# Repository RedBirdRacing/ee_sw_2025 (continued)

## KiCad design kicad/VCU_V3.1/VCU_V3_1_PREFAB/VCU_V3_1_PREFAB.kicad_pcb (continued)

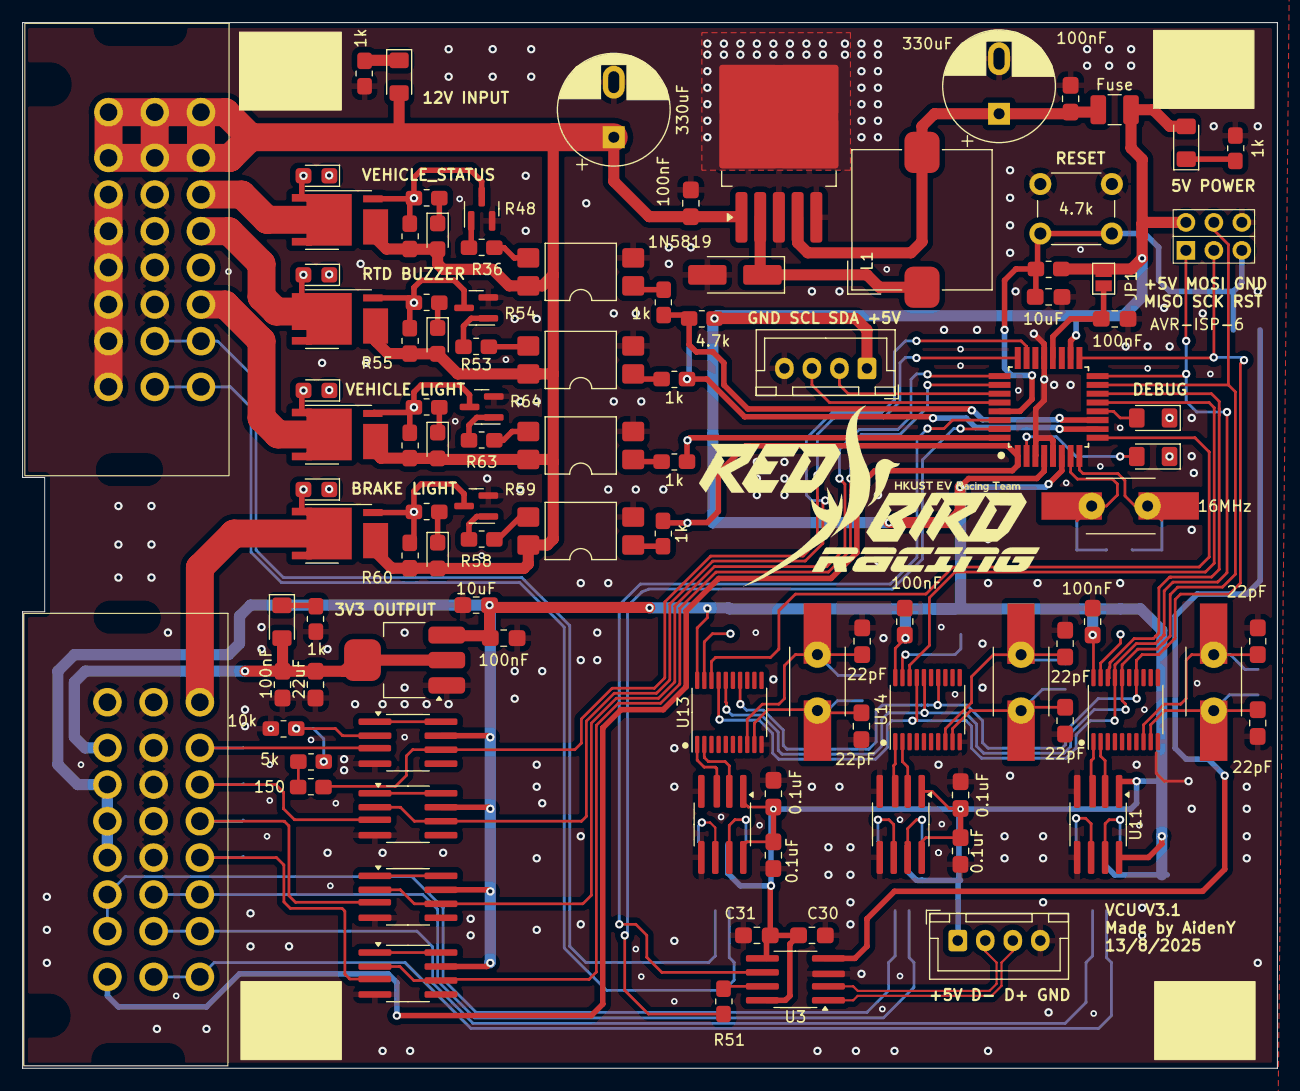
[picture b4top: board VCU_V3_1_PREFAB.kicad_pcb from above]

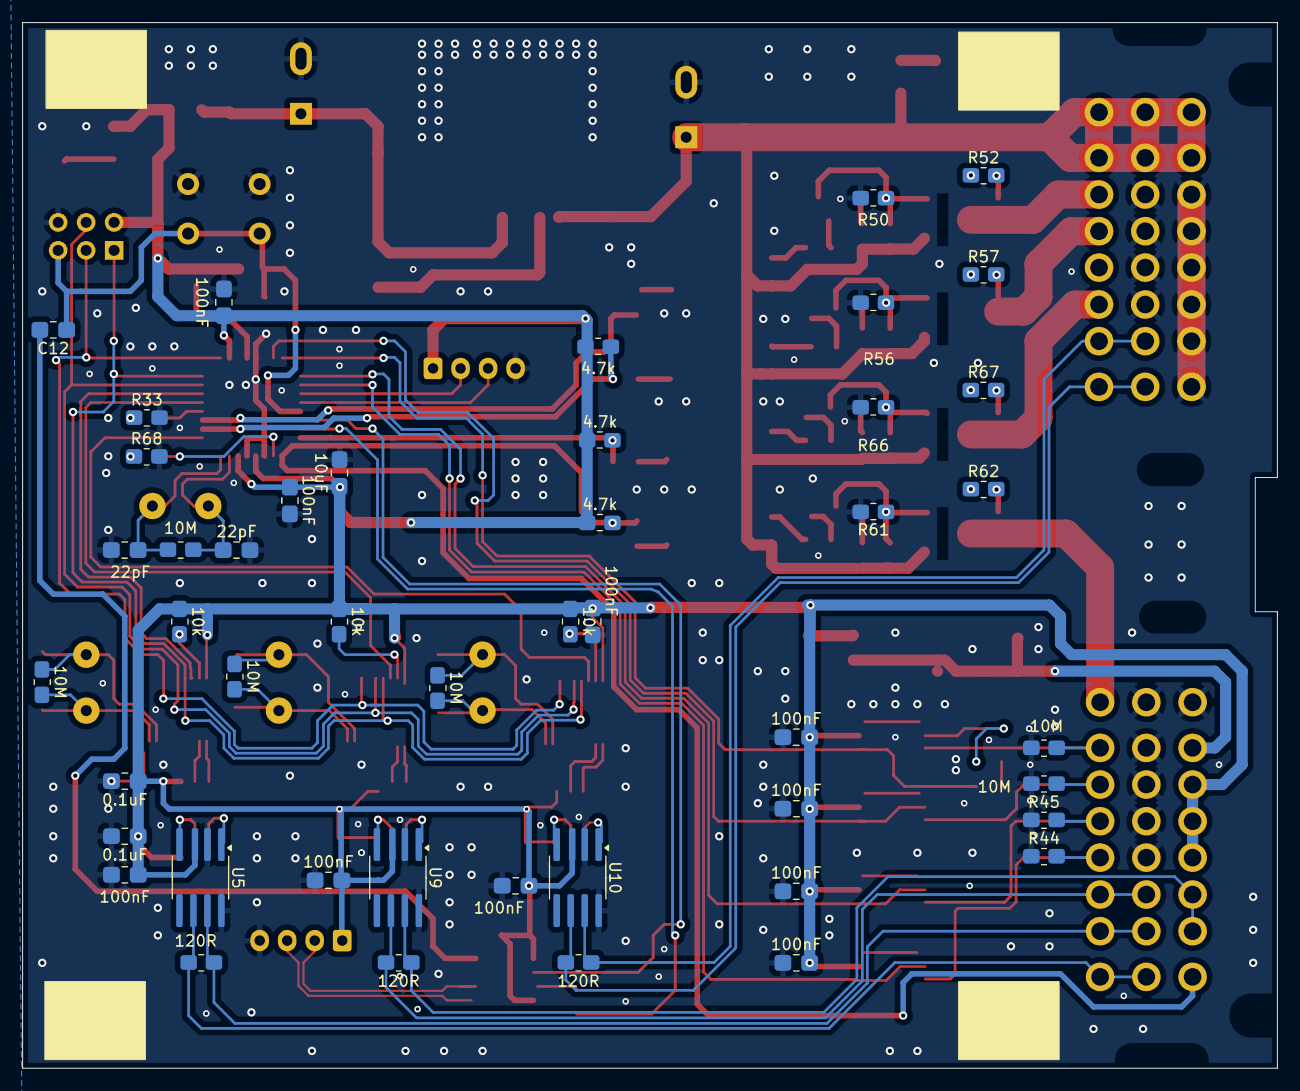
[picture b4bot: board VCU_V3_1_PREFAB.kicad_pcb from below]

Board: 2 copper layers, 114.0 x 95.0 mm, 152 parts (46 on the bottom side), 104 nets.

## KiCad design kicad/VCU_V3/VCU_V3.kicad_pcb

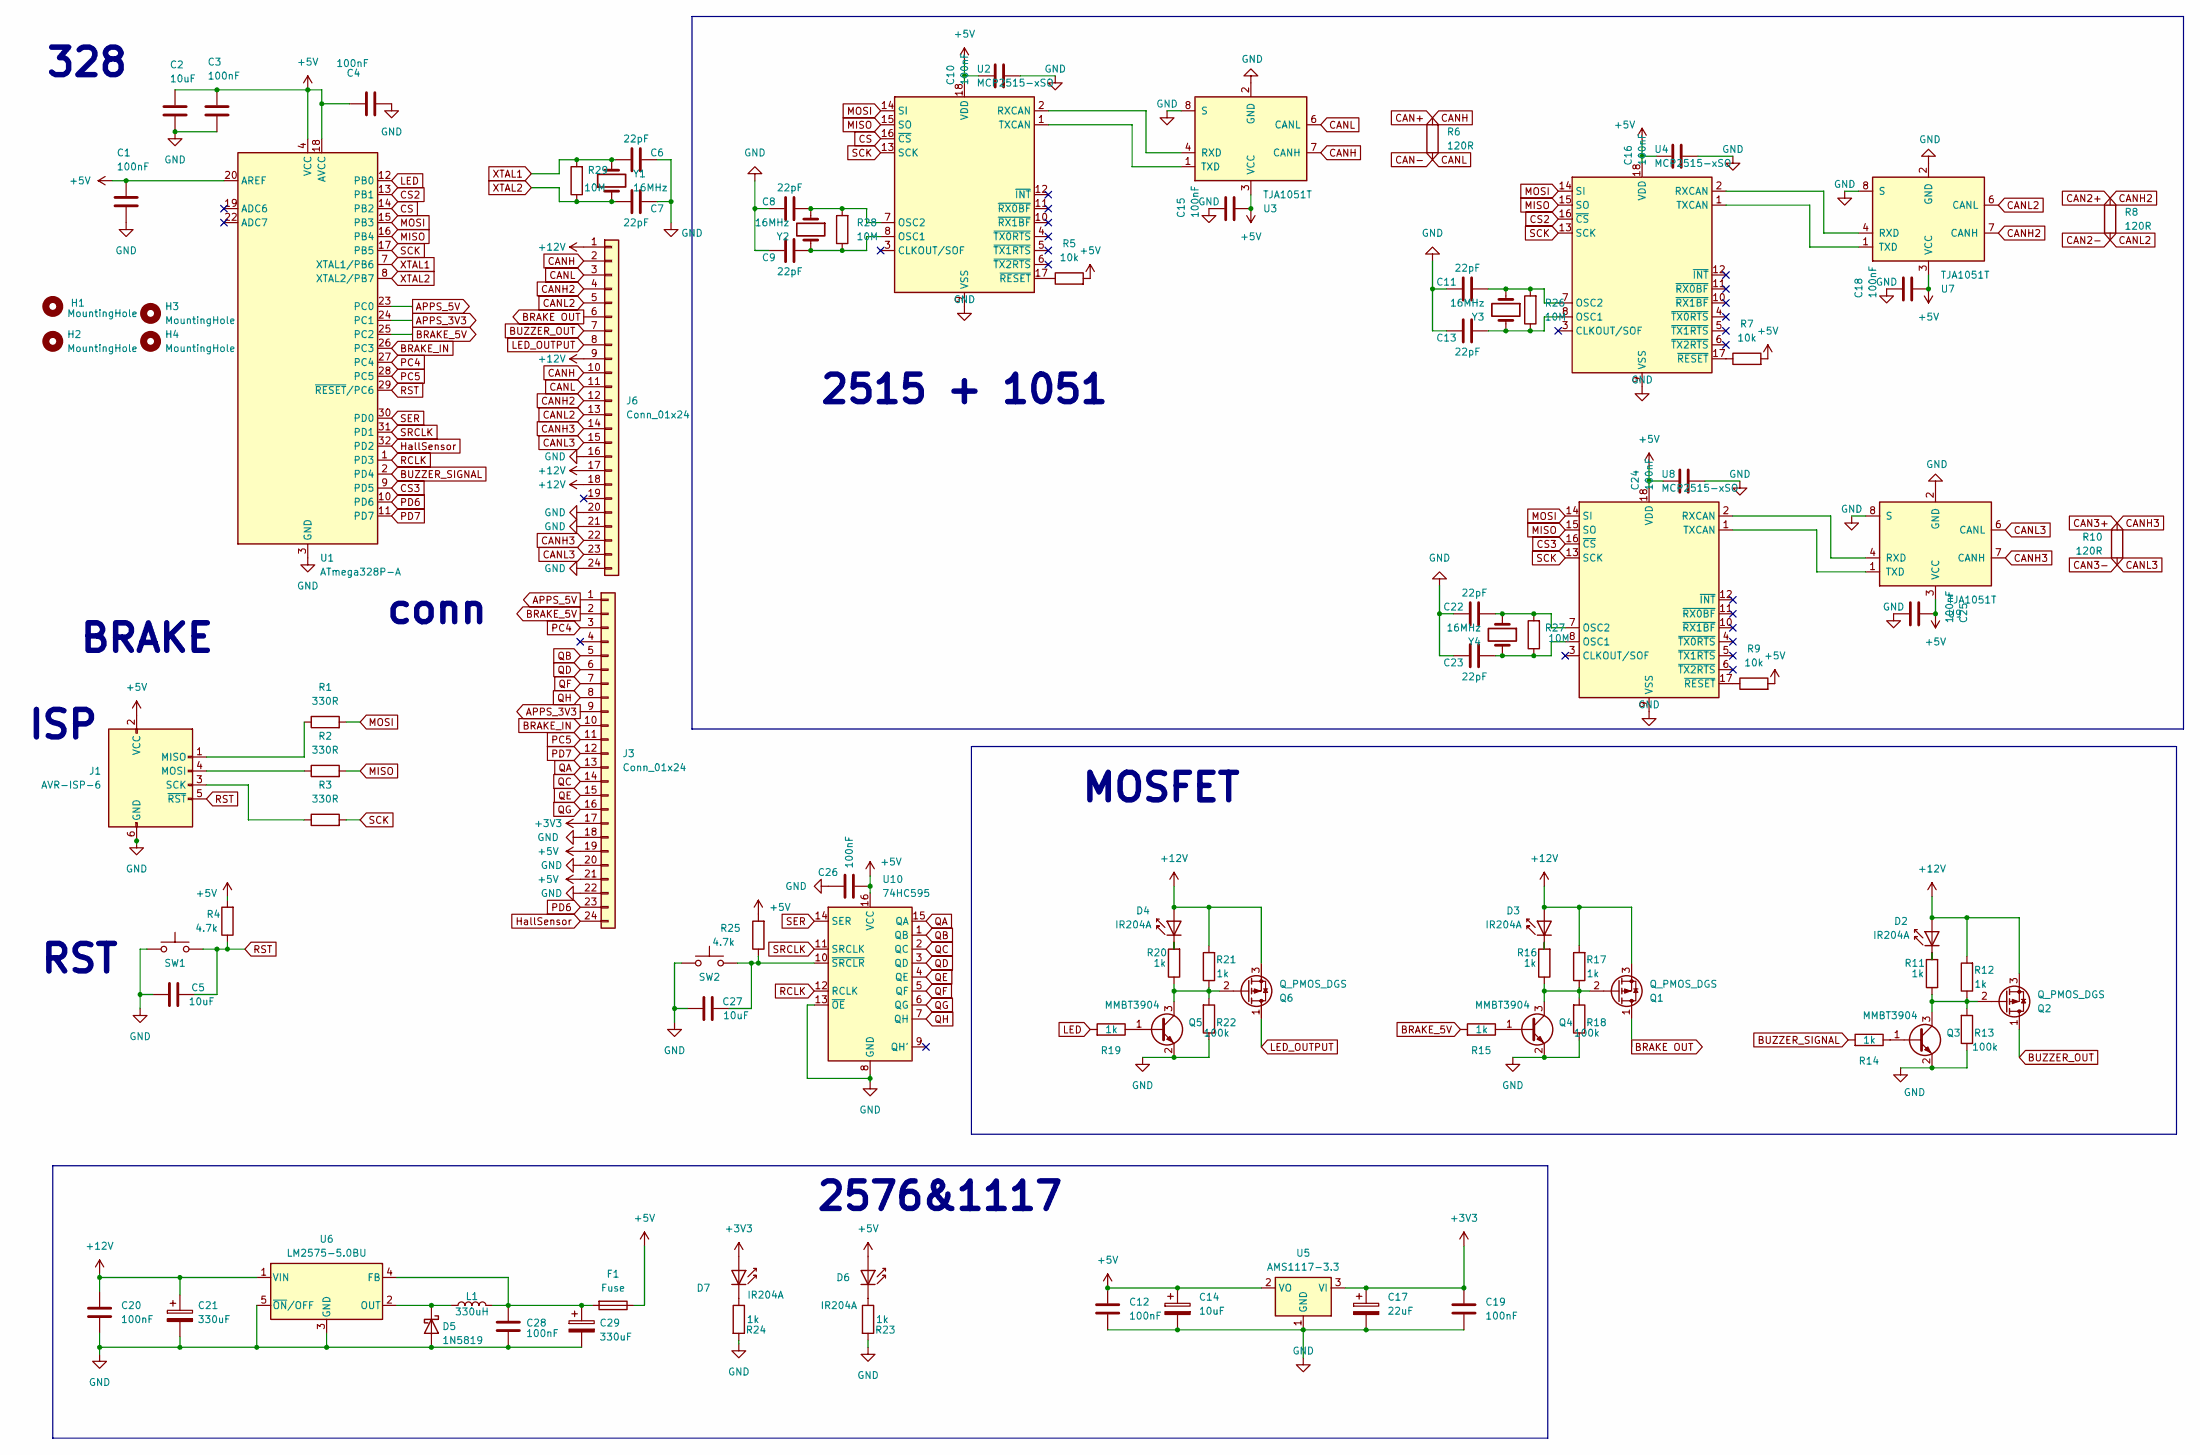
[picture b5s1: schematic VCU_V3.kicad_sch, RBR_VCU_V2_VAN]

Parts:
C1, C3, C4, C10, C12, C15, C16, C18, C19, C20, C24, C25, C26, C28: 100nF; C_0805_2012Metric_Pad1.18x1.45mm_HandSolder_L
C2, C5, C14, C27: 10uF; C_0805_2012Metric_Pad1.18x1.45mm_HandSolder_L
C6, C7, C8, C9, C11, C13, C22, C23: 22pF; C_0805_2012Metric_Pad1.18x1.45mm_HandSolder_L
C17: 22uF; C_0805_2012Metric_Pad1.18x1.45mm_HandSolder_L
C21, C29: 330uF; CP_Radial_D10.0mm_P5.00mm_F
D2, D3, D4, D6, D7: IR204A; LED_1206_3216Metric_Pad1.42x1.75mm_HandSolder
D5: 1N5819; D_SMA_Handsoldering
F1: Fuse; Fuse_1210_3225Metric_Pad1.42x2.65mm_HandSolder
H1, H2, H3, H4: MountingHole; MountingHole_3.2mm_M3
J1: AVR-ISP-6; PinHeader_2x03_P2.54mm_Vertical
J3, J6: Conn_01x24; HD241_24pin
L1: 330uH; L_10.4x10.4_H4.8
Q1, Q2, Q6: Q_PMOS_DGS; SOT-23
Q3, Q4, Q5: MMBT3904; SOT-23
R1, R2, R3: 330R; R_0805_2012Metric_Pad1.20x1.40mm_HandSolder_L
R4, R25: 4.7k; R_0805_2012Metric_Pad1.20x1.40mm_HandSolder_L
R5, R7, R9: 10k; R_0805_2012Metric_Pad1.20x1.40mm_HandSolder_L
R6, R8, R10: 120R; R_0805_2012Metric_Pad1.20x1.40mm_HandSolder_L
R11, R12, R14, R15, R16, R17, R19, R20, R21, R23, R24: 1k; R_0805_2012Metric_Pad1.20x1.40mm_HandSolder_L
R13, R18, R22: 100k; R_0805_2012Metric_Pad1.20x1.40mm_HandSolder_L
R26, R27, R28, R29: 10M; R_0805_2012Metric_Pad1.20x1.40mm_HandSolder_L
SW1, SW2: SW_Push; SW_PUSH_6mm_H5mm
U1: ATmega328P-A; TQFP-32_7x7mm_P0.8mm_L
U2, U4, U8: MCP2515-xSO; SOIC-18W_7.5x11.6mm_P1.27mm_L
U3, U7, U9: TJA1051T; SOIC-8_3.9x4.9mm_P1.27mm
U5: AMS1117-3.3; SOT-223-3_TabPin2
U6: LM2575-5.0BU; TO-263-5_TabPin3
U10: 74HC595; SOIC-16_3.9x9.9mm_P1.27mm
Y1, Y2, Y3, Y4: 16MHz; Crystal_HC49-U_Vertical_W_SMD

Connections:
+3V3: C17.1, C19.1, D7.2 (A), J3.17, U5.3 (VI)
+5V: C1.2, C2.2, C3.2, C4.2, C10.2, C12.1, C14.1, C15.1, C16.2, C18.1, C24.2, C25.2, C26.1, D6.2 (A), F1.1, J1.2 (VCC), J3.19, J3.21, R4.2, R5.2, R7.2, R9.2, R25.2, U1.4 (VCC), U1.6 (VCC), U1.18 (AVCC), U1.20 (AREF), U2.18 (VDD), U3.3 (VCC), U4.18 (VDD), U5.2 (VO), U7.3 (VCC), U8.18 (VDD), U9.3 (VCC), U10.16 (VCC)
+12V: C20.1, C21.1, D2.2 (A), D3.2 (A), D4.2 (A), J6.1, J6.9, J6.17, J6.18, Q1.3 (S), Q2.3 (S), Q6.3 (S), R12.2, R17.2, R21.2, U6.1 (VIN)
APPS_3V3: J3.9, U1.24 (PC1)
APPS_5V: J3.1, U1.23 (PC0)
BRAKE OUT: J6.6, Q1.1 (D)
BRAKE_5V: J3.2, R15.2, U1.25 (PC2)
BRAKE_IN: J3.10, U1.26 (PC3)
BUZZER_OUT: J6.7, Q2.1 (D)
BUZZER_SIGNAL: R14.2, U1.2 (PD4)
CAN2+: J6.4, J6.12, R8.2, U7.7 (CANH)
CAN2-: J6.5, J6.13, R8.1, U7.6 (CANL)
CAN3+: J6.14, J6.22, R10.2, U9.7 (CANH)
CAN3-: J6.15, J6.23, R10.1, U9.6 (CANL)
CAN+: J6.2, J6.10, R6.2, U3.7 (CANH)
CAN-: J6.3, J6.11, R6.1, U3.6 (CANL)
CS: U1.14 (PB2), U2.16 (~CS)
CS2: U1.13 (PB1), U4.16 (~CS)
CS3: U1.9 (PD5), U8.16 (~CS)
GND: C1.1, C2.1, C3.1, C4.1, C5.1, C6.1, C7.1, C8.1, C9.1, C10.1, C11.1, C12.2, C13.1, C14.2, C15.2, C16.1, C17.2, C18.2, C19.2, C20.2, C21.2, C22.1, C23.1, C24.1, C25.1, C26.2, C27.1, C28.2, C29.2, D5.2 (A), J1.6 (GND), J3.18, J3.20, J3.22, J6.16, J6.20, J6.21, J6.24, Q3.2 (E), Q4.2 (E), Q5.2 (E), R13.1, R18.1, R22.1, R23.2, R24.2, SW1.1, SW2.1, U1.3 (GND), U1.5 (GND), U1.21 (GND), U2.9 (VSS), U3.2 (GND), U3.8 (S), U4.9 (VSS), U5.1 (GND), U6.3 (GND), U6.5 (~ON/OFF), U7.2 (GND), U7.8 (S), U8.9 (VSS), U9.2 (GND), U9.8 (S), U10.8 (GND), U10.13 (~OE)
HallSensor: J3.24, U1.32 (PD2)
LED: R19.2, U1.12 (PB0)
LED_OUTPUT: J6.8, Q6.1 (D)
MISO: R2.2, U1.16 (PB4), U2.15 (SO), U4.15 (SO), U8.15 (SO)
MOSI: R1.2, U1.15 (PB3), U2.14 (SI), U4.14 (SI), U8.14 (SI)
unnamed: D2.1 (K), R11.2
unnamed: D3.1 (K), R16.2
unnamed: D4.1 (K), R20.2
unnamed: D5.1 (K), L1.1, U6.2 (OUT)
unnamed: D6.1 (K), R23.1
unnamed: D7.1 (K), R24.1
unnamed: J1.1 (MISO), R1.1
unnamed: J1.4 (MOSI), R2.1
unnamed: J1.3 (SCK), R3.1
unnamed: Q1.2 (G), Q4.3 (C), R16.1, R17.1, R18.2
unnamed: Q2.2 (G), Q3.3 (C), R11.1, R12.1, R13.2
unnamed: Q3.1 (B), R14.1
unnamed: Q4.1 (B), R15.1
unnamed: Q5.1 (B), R19.1
unnamed: Q5.3 (C), Q6.2 (G), R20.1, R21.1, R22.2
unnamed: C9.2, R28.1, U2.8 (OSC1), Y2.2
unnamed: C8.2, R28.2, U2.7 (OSC2), Y2.1
unnamed: U2.2 (RXCAN), U3.4 (RXD)
unnamed: U2.1 (TXCAN), U3.1 (TXD)
unnamed: R5.1, U2.17 (~RESET)
unnamed: C13.2, R26.1, U4.8 (OSC1), Y3.2
unnamed: C11.2, R26.2, U4.7 (OSC2), Y3.1
unnamed: U4.2 (RXCAN), U7.4 (RXD)
unnamed: U4.1 (TXCAN), U7.1 (TXD)
unnamed: R7.1, U4.17 (~RESET)
unnamed: C28.1, C29.1, F1.2, L1.2, U6.4 (FB)
unnamed: C23.2, R27.1, U8.8 (OSC1), Y4.2
unnamed: C22.2, R27.2, U8.7 (OSC2), Y4.1
unnamed: U8.2 (RXCAN), U9.4 (RXD)
unnamed: U8.1 (TXCAN), U9.1 (TXD)
unnamed: R9.1, U8.17 (~RESET)
unnamed: C27.2, R25.1, SW2.2, U10.10 (~SRCLR)
PC4: J3.3, U1.27 (PC4)
PC5: J3.11, U1.28 (PC5)
PD6: J3.23, U1.10 (PD6)
PD7: J3.12, U1.11 (PD7)
QA: J3.13, U10.15 (QA)
QB: J3.5, U10.1 (QB)
QC: J3.14, U10.2 (QC)
QD: J3.6, U10.3 (QD)
QE: J3.15, U10.4 (QE)
QF: J3.7, U10.5 (QF)
QG: J3.16, U10.6 (QG)
QH: J3.8, U10.7 (QH)
RCLK: U1.1 (PD3), U10.12 (RCLK)
RST: C5.2, J1.5 (~RST), R4.1, SW1.2, U1.29 (~RESET/PC6)
SCK: R3.2, U1.17 (PB5), U2.13 (SCK), U4.13 (SCK), U8.13 (SCK)
SER: U1.30 (PD0), U10.14 (SER)
SRCLK: U1.31 (PD1), U10.11 (SRCLK)
XTAL1: C6.2, R29.2, U1.7 (XTAL1/PB6), Y1.2
XTAL2: C7.2, R29.1, U1.8 (XTAL2/PB7), Y1.1

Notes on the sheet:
RST
conn
ISP
2576&1117
MOSFET
2515 + 1051
BRAKE
328

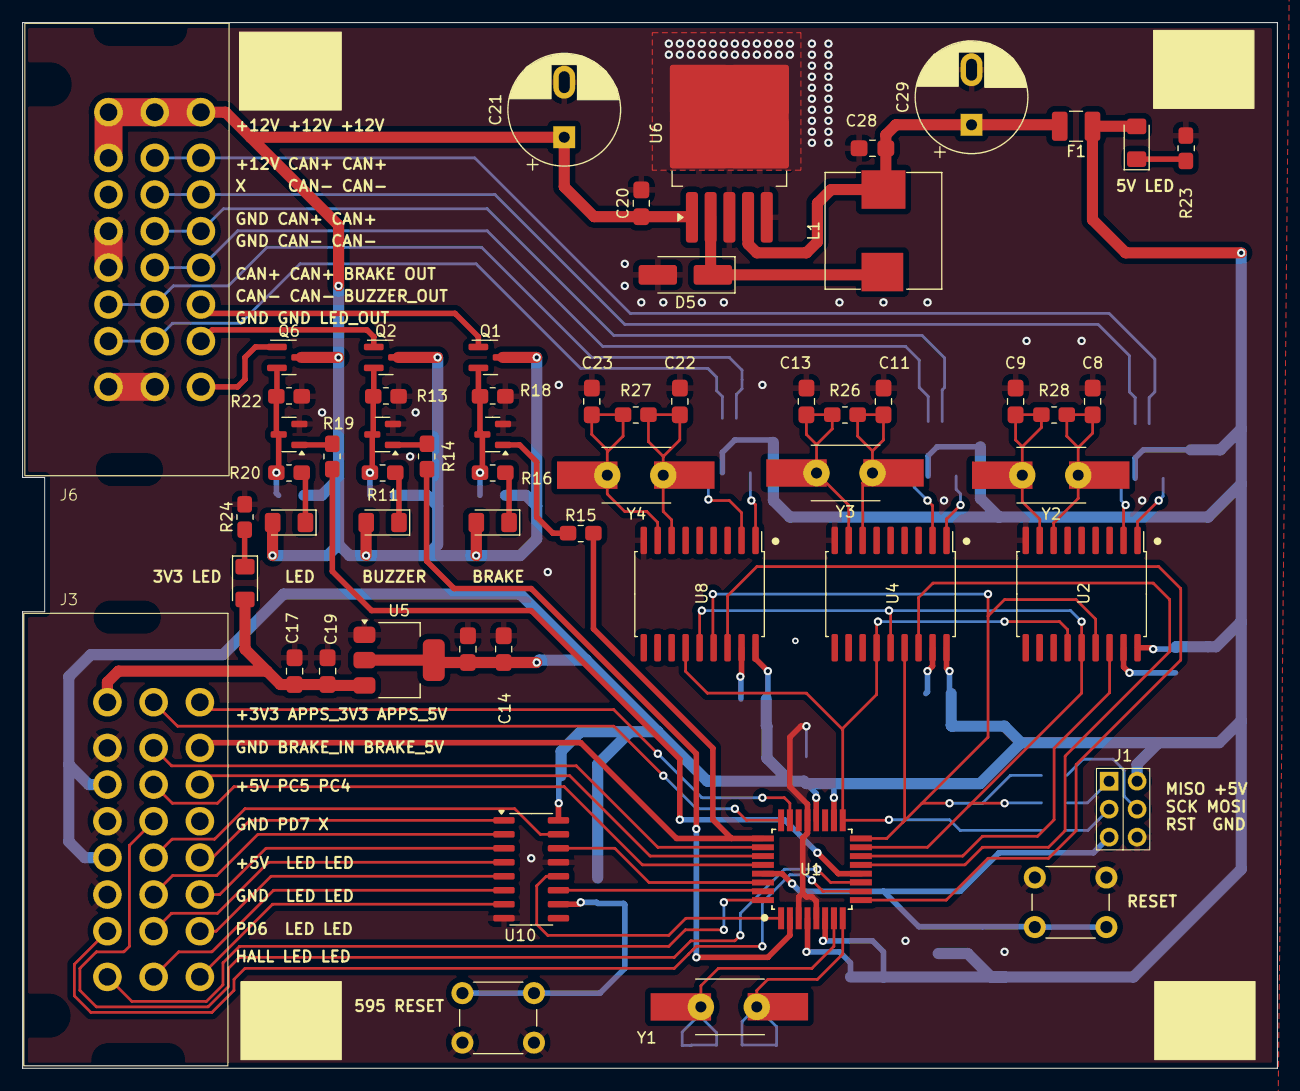
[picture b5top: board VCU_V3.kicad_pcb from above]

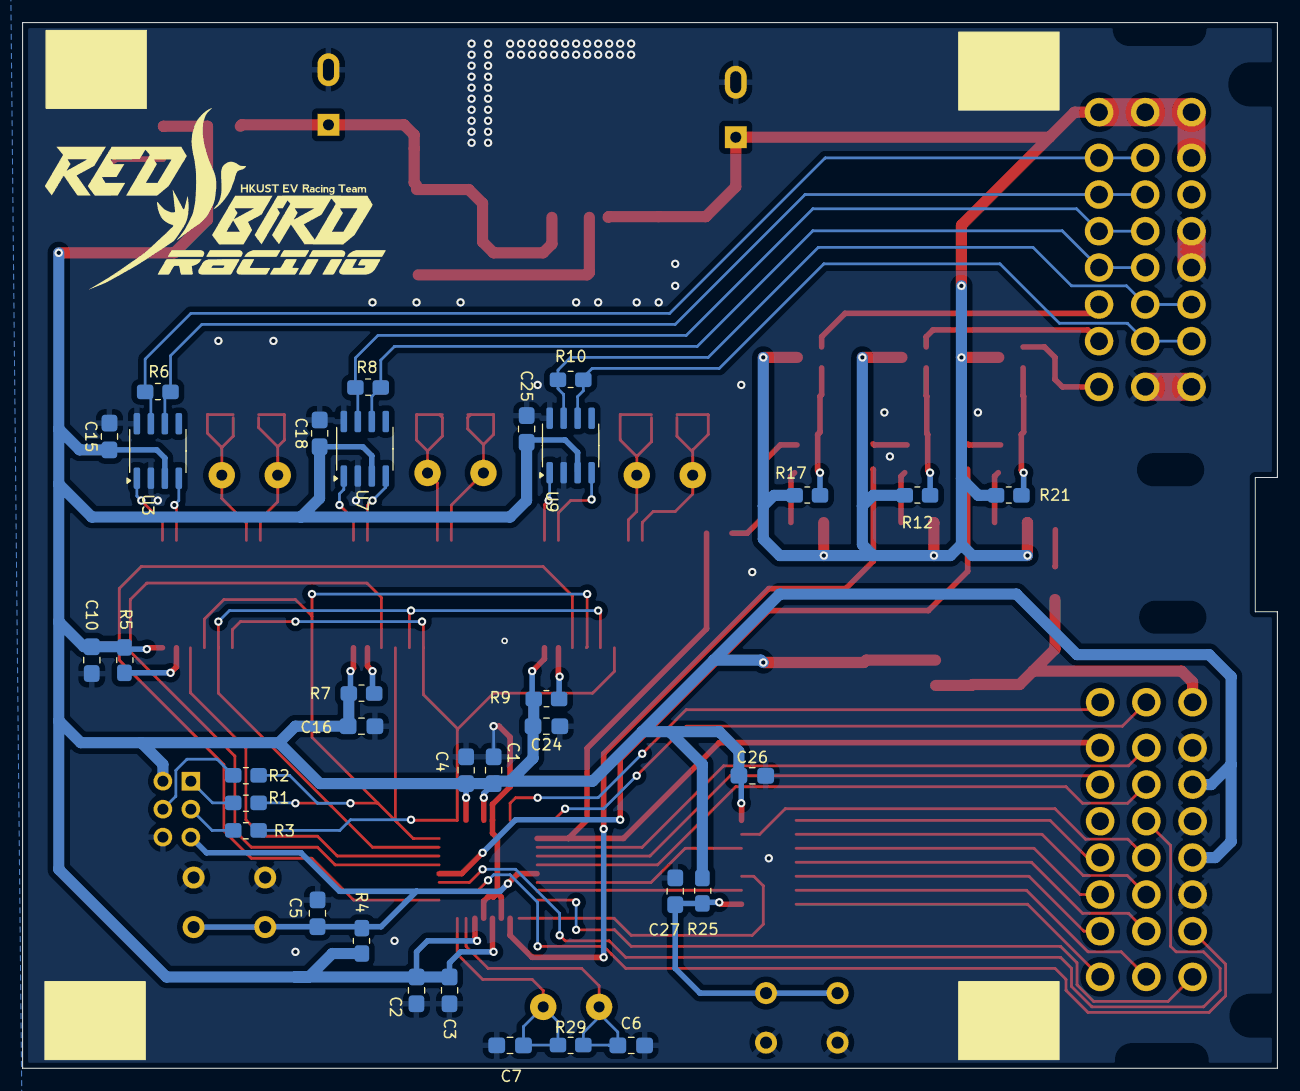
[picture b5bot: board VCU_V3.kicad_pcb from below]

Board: 2 copper layers, 114.0 x 95.0 mm, 95 parts (33 on the bottom side), 76 nets.

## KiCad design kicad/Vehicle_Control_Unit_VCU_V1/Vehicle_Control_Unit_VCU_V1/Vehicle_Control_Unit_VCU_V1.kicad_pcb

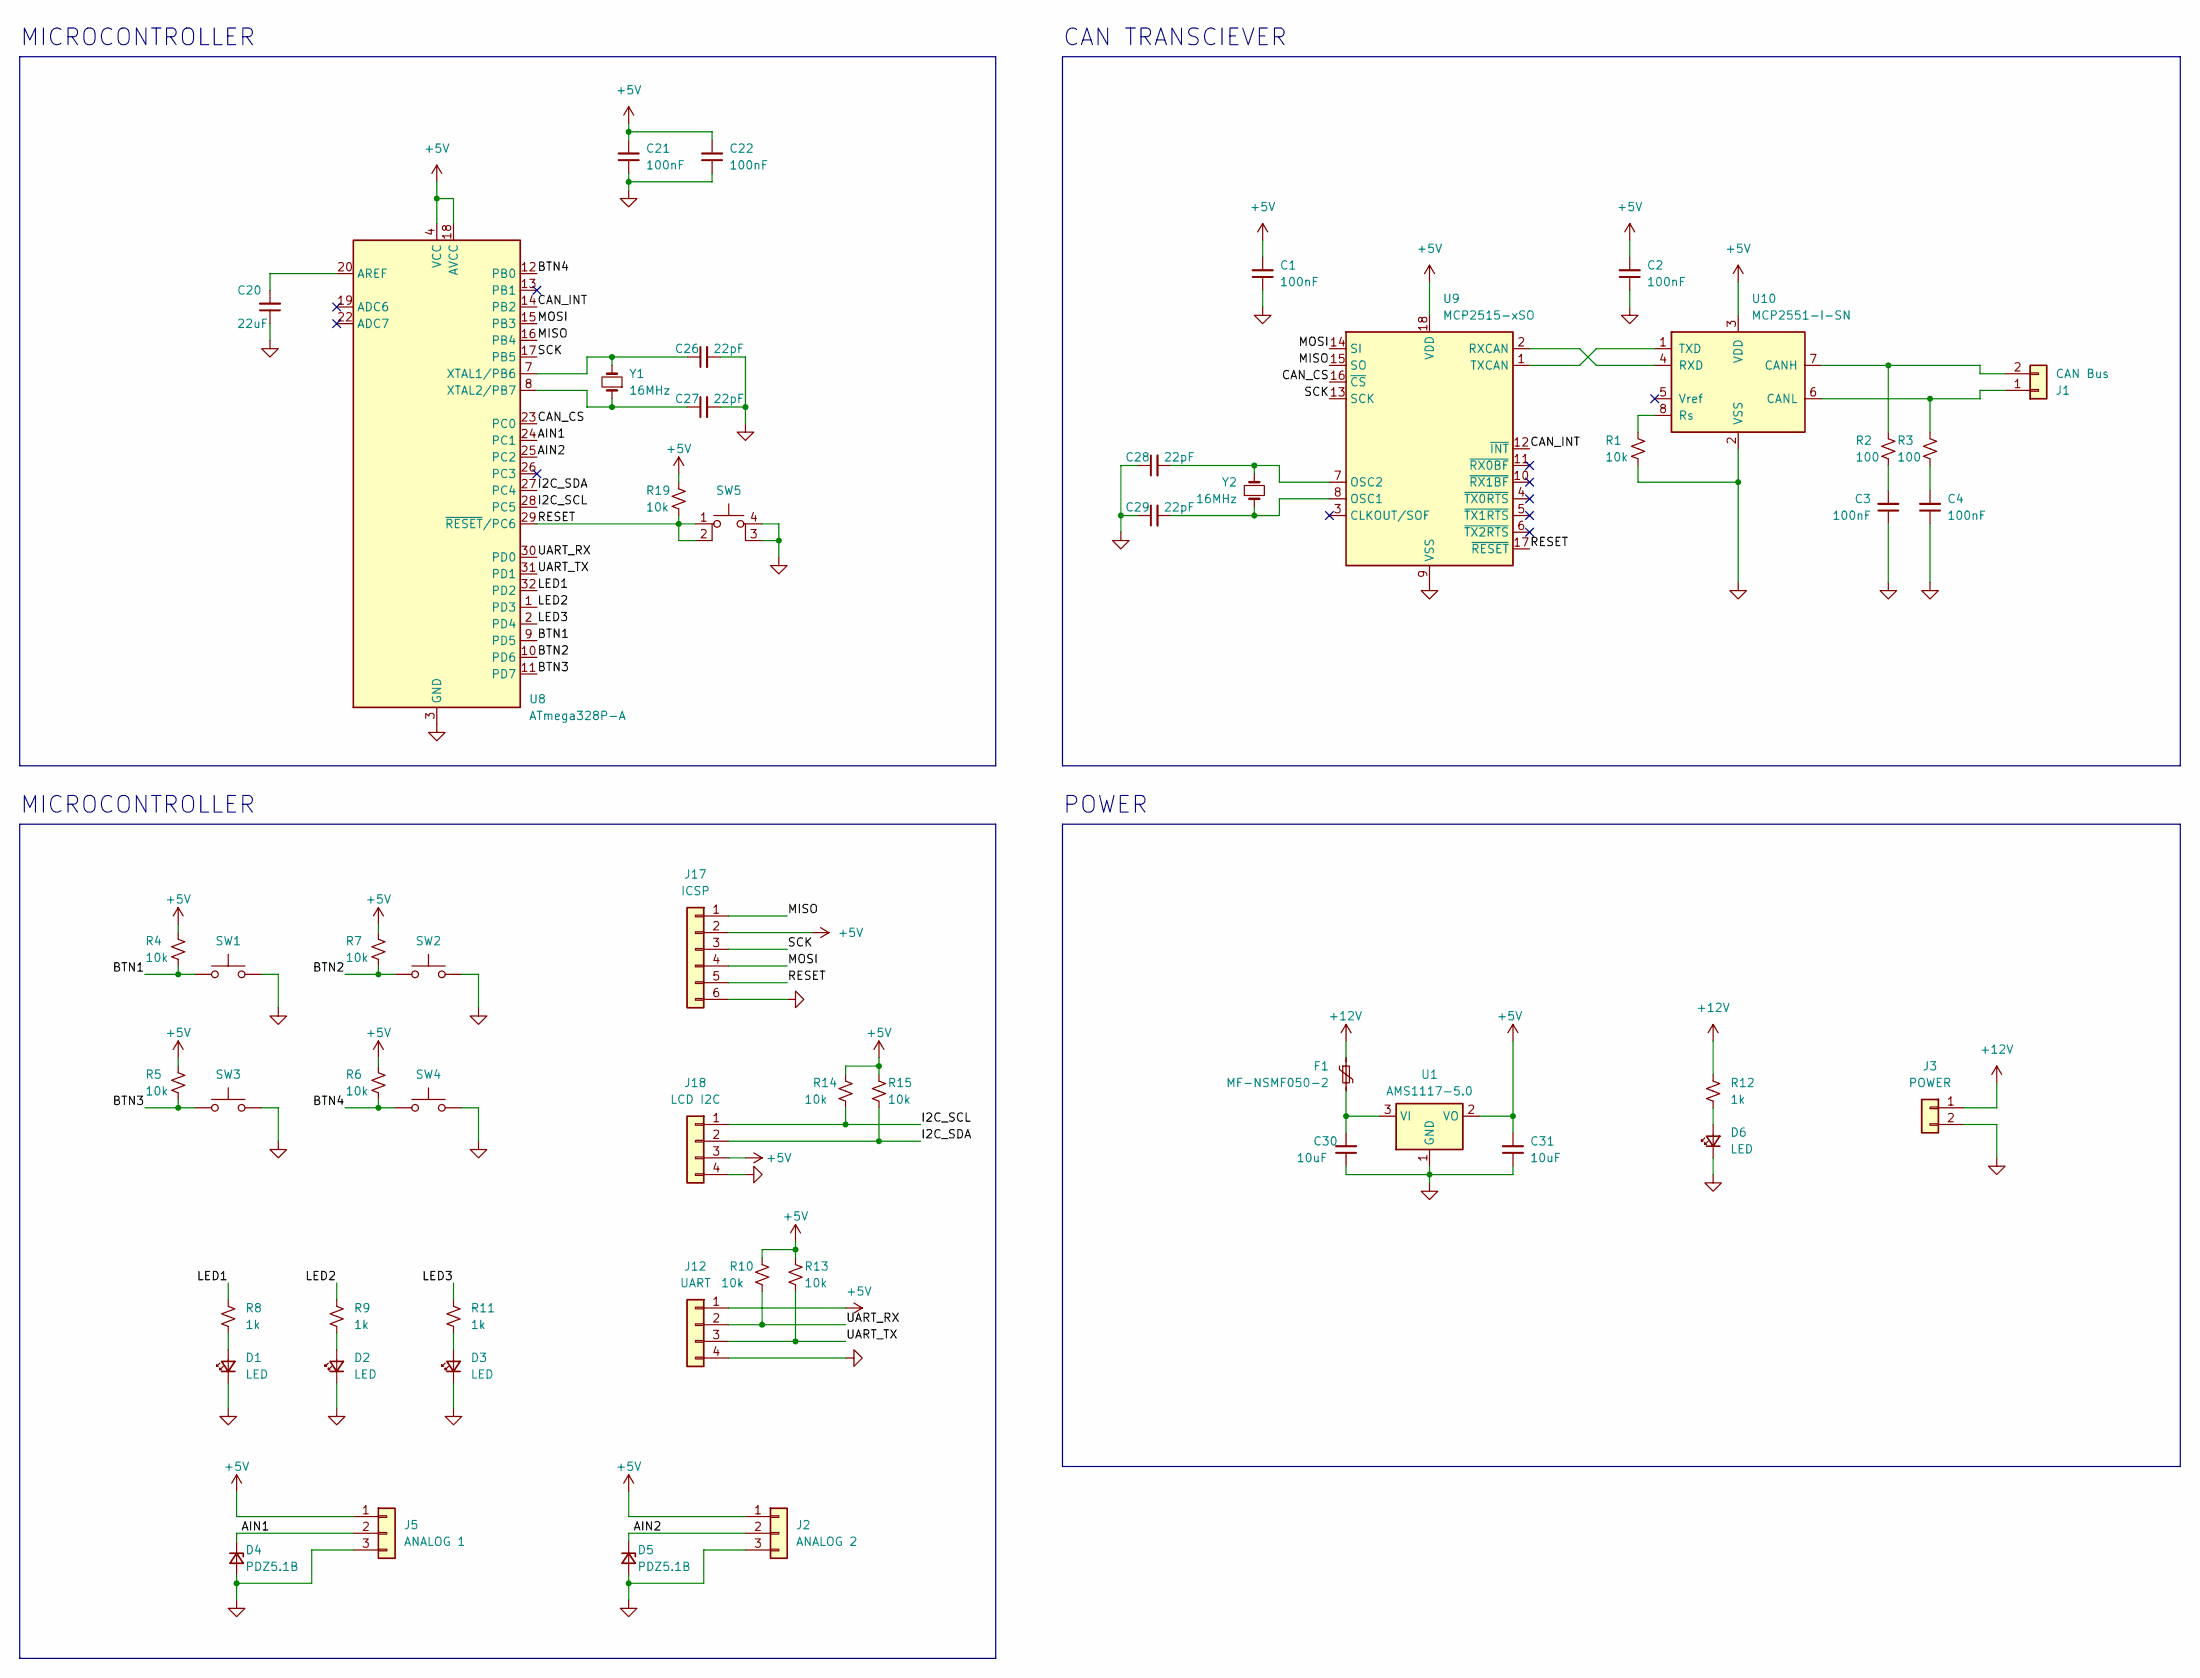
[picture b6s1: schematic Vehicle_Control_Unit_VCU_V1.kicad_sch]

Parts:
C1, C2, C3, C4, C21, C22: 100nF; C_0805_2012Metric
C20: 22uF; C_0805_2012Metric
C26, C27, C28, C29: 22pF; C_0805_2012Metric
C30, C31: 10uF; C_0805_2012Metric
D1, D2, D3: LED; JST_XH_S2B-XH-A-1_1x02_P2.50mm_Horizontal
D4, D5: PDZ5.1B; D_SOD-323
D6: LED; LED_D3.0mm
F1: MF-NSMF050-2; Fuse_1206_3216Metric
J1: CAN Bus; JST_XH_S2B-XH-A-1_1x02_P2.50mm_Horizontal
J2: ANALOG 2; JST_XH_S3B-XH-A-1_1x03_P2.50mm_Horizontal
J3: POWER; JST_XH_S2B-XH-A-1_1x02_P2.50mm_Horizontal
J5: ANALOG 1; JST_XH_S3B-XH-A-1_1x03_P2.50mm_Horizontal
J12: UART; PinHeader_1x04_P2.54mm_Vertical
J17: ICSP; PinHeader_2x03_P2.54mm_Vertical
J18: LCD I2C; PinSocket_1x04_P2.54mm_Vertical
R1, R4, R5, R6, R7, R10, R13, R14, R15, R19: 10k; R_0805_2012Metric
R2, R3: 100; R_0805_2012Metric
R8, R9, R11, R12: 1k; R_0805_2012Metric
SW1, SW2, SW3, SW4: SW_Push; JST_XH_S2B-XH-A-1_1x02_P2.50mm_Horizontal
SW5: SW_MEC_5E; TL3342F260QG
U1: AMS1117-5.0; SOT-223-3_TabPin2
U8: ATmega328P-A; TQFP-32_7x7mm_P0.8mm
U9: MCP2515-xSO; SOIC-18W_7.5x11.6mm_P1.27mm
U10: MCP2551-I-SN; SOIC-8_3.9x4.9mm_P1.27mm
Y1, Y2: 16MHz; Crystal_SMD_5032-2Pin_5.0x3.2mm_HandSoldering

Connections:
+5V: C1.2, C2.2, C21.2, C22.2, C31.2, J2.1, J5.1, J12.1, J17.2, J18.3, R4.1, R5.1, R6.1, R7.1, R10.1, R13.1, R14.1, R15.1, R19.1, U1.2 (VO), U8.4 (VCC), U8.6 (VCC), U8.18 (AVCC), U9.18 (VDD), U10.3 (VDD)
+12V: F1.1, J3.1, R12.1
/AIN1: D4.1 (K), J5.2, U8.24 (PC1)
/AIN2: D5.1 (K), J2.2, U8.25 (PC2)
/BTN1: R4.2, SW1.1, U8.9 (PD5)
/BTN2: R7.2, SW2.1, U8.10 (PD6)
/BTN3: R5.2, SW3.1, U8.11 (PD7)
/BTN4: R6.2, SW4.1, U8.12 (PB0)
/CAN_CS: U8.23 (PC0), U9.16 (~CS)
/CAN_INT: U8.14 (PB2), U9.12 (~INT)
/I2C_SCL: J18.1, R14.2, U8.28 (PC5)
/I2C_SDA: J18.2, R15.2, U8.27 (PC4)
/LED1: R8.1, U8.32 (PD2)
/LED2: R9.1, U8.1 (PD3)
/LED3: R11.1, U8.2 (PD4)
/MISO: J17.1, U8.16 (PB4), U9.15 (SO)
/MOSI: J17.4, U8.15 (PB3), U9.14 (SI)
/RESET: J17.5, R19.2, SW5.1, SW5.2, U8.29 (~RESET/PC6), U9.17 (~RESET)
/SCK: J17.3, U8.17 (PB5), U9.13 (SCK)
/UART_RX: J12.2, R10.2, U8.30 (PD0)
/UART_TX: J12.3, R13.2, U8.31 (PD1)
GND: C1.1, C2.1, C3.1, C4.1, C20.1, C21.1, C22.1, C26.2, C27.2, C28.1, C29.1, C30.1, C31.1, D1.1 (K), D2.1 (K), D3.1 (K), D4.2 (A), D5.2 (A), D6.1 (K), J2.3, J3.2, J5.3, J12.4, J17.6, J18.4, R1.2, SW1.2, SW2.2, SW3.2, SW4.2, SW5.3 (K), SW5.4 (A), U1.1 (GND), U8.3 (GND), U8.5 (GND), U8.21 (GND), U9.9 (VSS), U10.2 (VSS)
unnamed: C3.2, R2.2
unnamed: C4.2, R3.2
unnamed: D1.2 (A), R8.2
unnamed: D2.2 (A), R9.2
unnamed: D3.2 (A), R11.2
unnamed: D6.2 (A), R12.2
unnamed: J1.1, R3.1, U10.6 (CANL)
unnamed: J1.2, R2.1, U10.7 (CANH)
unnamed: C30.2, F1.2, U1.3 (VI)
unnamed: C20.2, U8.20 (AREF)
unnamed: C26.1, U8.7 (XTAL1/PB6), Y1.2
unnamed: C27.1, U8.8 (XTAL2/PB7), Y1.1
unnamed: C29.2, U9.8 (OSC1), Y2.1
unnamed: C28.2, U9.7 (OSC2), Y2.2
unnamed: U9.2 (RXCAN), U10.4 (RXD)
unnamed: R1.1, U10.8 (Rs)
unnamed: U9.1 (TXCAN), U10.1 (TXD)

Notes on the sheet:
POWER
CAN TRANSCIEVER
MICROCONTROLLER

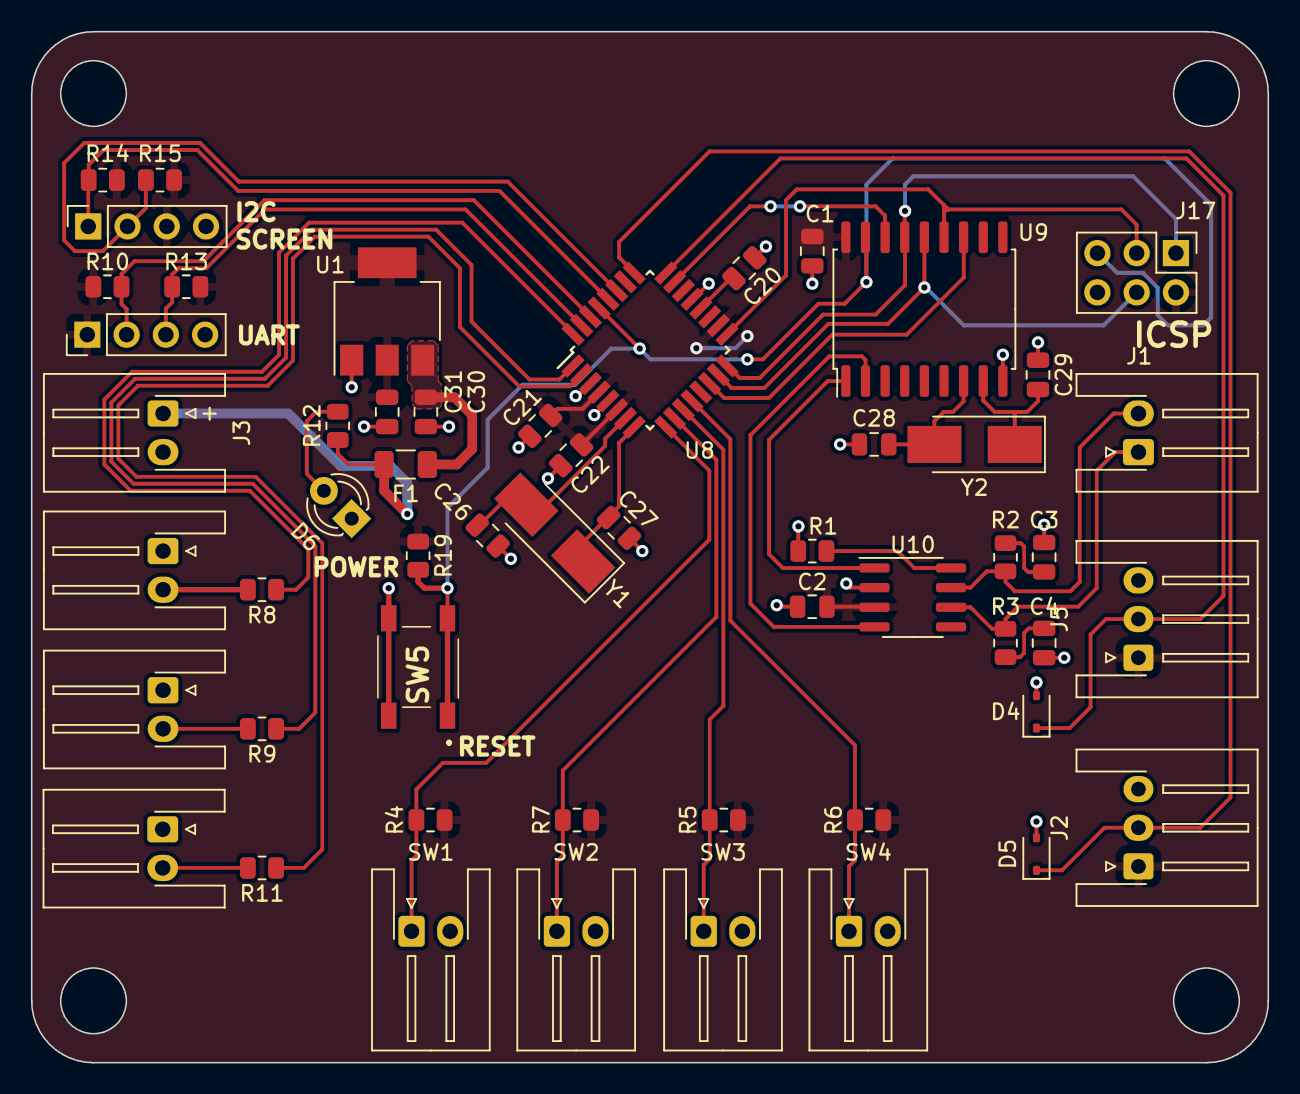
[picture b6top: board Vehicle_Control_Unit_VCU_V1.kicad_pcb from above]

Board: 2 copper layers, 80.0 x 66.7 mm, 54 parts (0 on the bottom side), 39 nets.

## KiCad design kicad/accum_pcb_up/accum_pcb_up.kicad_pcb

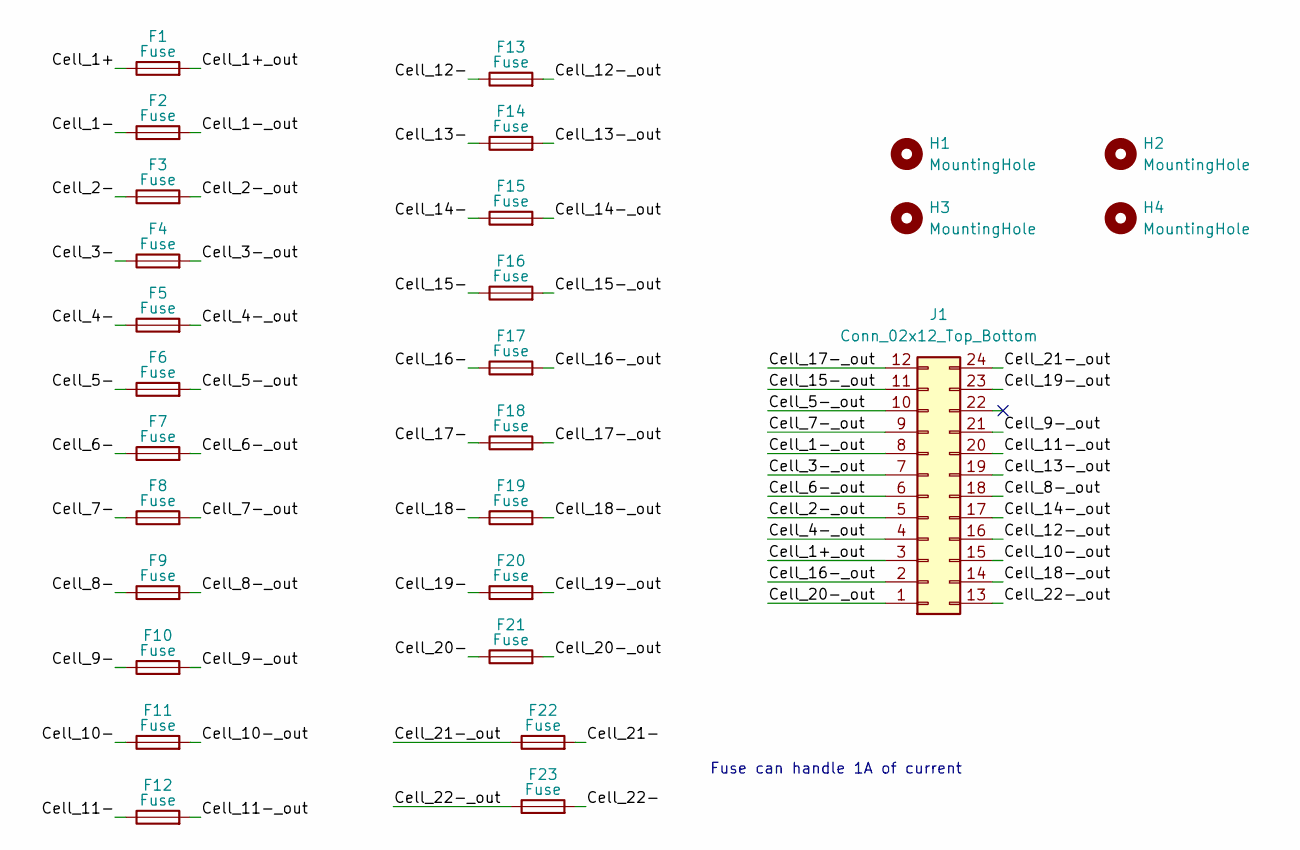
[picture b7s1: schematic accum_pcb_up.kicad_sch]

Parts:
F1, F2, F3, F4, F5, F6, F7, F8, F9, F10, F11, F12, F13, F14, F15, F16, F17, F18, F19, F20, F21, F22, F23: Fuse; Fuse_Littelfuse-NANO2-885
H1, H2, H3, H4: MountingHole; MountingHole_4.3mm_M4
J1: Conn_02x12_Top_Bottom; Molex_Micro-Fit_3.0_43045-2412_2x12_P3.00mm_Vertical

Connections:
/Cell_1+: F1.1
/Cell_1+_out: F1.2, J1.3
/Cell_1-: F2.1
/Cell_1-_out: F2.2, J1.8
/Cell_2-: F3.1
/Cell_2-_out: F3.2, J1.5
/Cell_3-: F4.1
/Cell_3-_out: F4.2, J1.7
/Cell_4-: F5.1
/Cell_4-_out: F5.2, J1.4
/Cell_5-: F6.1
/Cell_5-_out: F6.2, J1.10
/Cell_6-: F7.1
/Cell_6-_out: F7.2, J1.6
/Cell_7-: F8.1
/Cell_7-_out: F8.2, J1.9
/Cell_8-: F9.1
/Cell_8-_out: F9.2, J1.18
/Cell_9-: F10.1
/Cell_9-_out: F10.2, J1.21
/Cell_10-: F11.1
/Cell_10-_out: F11.2, J1.15
/Cell_11-: F12.1
/Cell_11-_out: F12.2, J1.20
/Cell_12-: F13.1
/Cell_12-_out: F13.2, J1.16
/Cell_13-: F14.1
/Cell_13-_out: F14.2, J1.19
/Cell_14-: F15.1
/Cell_14-_out: F15.2, J1.17
/Cell_15-: F16.1
/Cell_15-_out: F16.2, J1.11
/Cell_16-: F17.1
/Cell_16-_out: F17.2, J1.2
/Cell_17-: F18.1
/Cell_17-_out: F18.2, J1.12
/Cell_18-: F19.1
/Cell_18-_out: F19.2, J1.14
/Cell_19-: F20.1
/Cell_19-_out: F20.2, J1.23
/Cell_20-: F21.1
/Cell_20-_out: F21.2, J1.1
/Cell_21-: F22.2
/Cell_21-_out: F22.1, J1.24
/Cell_22-: F23.2
/Cell_22-_out: F23.1, J1.13

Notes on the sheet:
Fuse can handle 1A of current

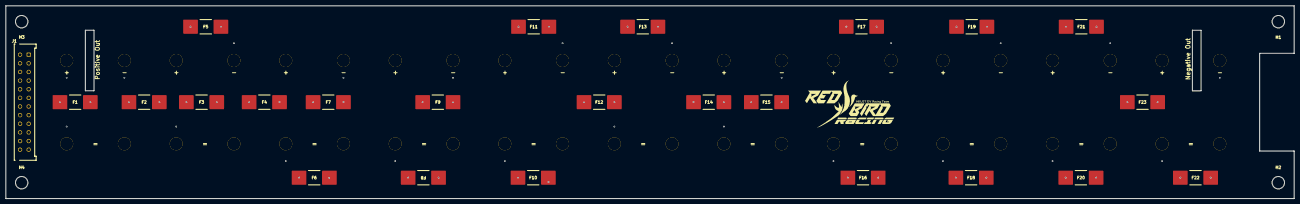
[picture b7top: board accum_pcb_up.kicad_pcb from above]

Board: 4 copper layers, 447.5 x 66.9 mm, 28 parts (0 on the bottom side), 23 nets.
